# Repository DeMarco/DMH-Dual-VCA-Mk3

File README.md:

# DMH-Dual-VCA-Mk3
Version 3 of my stereo VCA in Kosmo format, now including voltage controlled panning and optional clipping and distortion!

## Features

- 2 channels, A and B
- 2 CV inputs per channel, each one with its own attenuverter knob
- Unipolar control voltage: 0V means VCA is fully closed (gain = 0), +10V means completely open (gain = 1)
- 1 offset knob per channel, useful to bias bipolar CV signals like those from LFOs
- The offset setting and attenuverted CV inputs of each channel are summed
- Toggle switches to select between pan/balanced/tremolo mode, and clipping/distortion
- Pan mode: output volue of both channels is halved. Pan CV signal will increase one channel's volume and decrease the other's simultaneously.
- Balanced mode: same as Pan mode, but both channels volume are biased with half the Pan CV signal amplitude, which preserves overall volume during panning.
- Tremolo mode: both channels duck in response to Pan CV.
- The Pan knob can be used to manually change panning when no Pan CV is plugged in. It becomes an attenuverter when Pan CV is used.
- Clip mode: 4v7 Zener diode pairs are applied to both channel outputs, effectively limiting output to about +/-5V.
- Distorted mode: 3v0 Zener diode pairs and 2x gain is applied to both channels output, effectively distorting and limiting output to +/-5V.
- LEDs indicate when the output levels pre-clipping/distortion peak above 5V, so you know that Clip mode is clipping the output when engaged.

Demo video: https://www.instagram.com/reel/DbrHDk0sg0o/?utm_source=ig_web_copy_link&igsh=MzRlODBiNWFlZA==

## Schematic and Gerbers

https://github.com/DeMarco/DMH-Dual-VCA-Mk3/blob/main/Schematic.pdf

https://github.com/DeMarco/DMH-Dual-VCA-Mk3/tree/main/Gerbers

https://github.com/DeMarco/DMH-Dual-VCA-Mk3/blob/main/DMH_Output_BoM.csv

Please note the plug-in VCA submodules are part of another Repo. You need to make 4 of these to assemble the complete module:

https://github.com/DeMarco/DMH-Submodules/tree/main/DMH_Submodule_VCA/Gerbers

## Assembly instructions

Use 11mm long pin headers on the Main PCB to ensure connection with the pin sockets on the Controls PCB.
Other than that, nothing special.
I recommend soldering components in order of height: start with resistors and diodes, then move on to IC sockets, capacitors, transistors and connectors.

### Main PCB

### Controls PCB

### VCA Submodule Mk1

## Calibration

### Attenuverters pot center

t.b.w.

### VCAs symmetry

t.b.w

## Current consumption

+12V --> 38mA

-12V --> 38mA

## Dimensions

Height: 20cm

Width: 5cm

Depth: t.b.c.

## Font

For viewing/customizing in KiCad, I recommend downloading and installing the Nulshock font from Typodermic: https://typodermicfonts.com/nulshock/

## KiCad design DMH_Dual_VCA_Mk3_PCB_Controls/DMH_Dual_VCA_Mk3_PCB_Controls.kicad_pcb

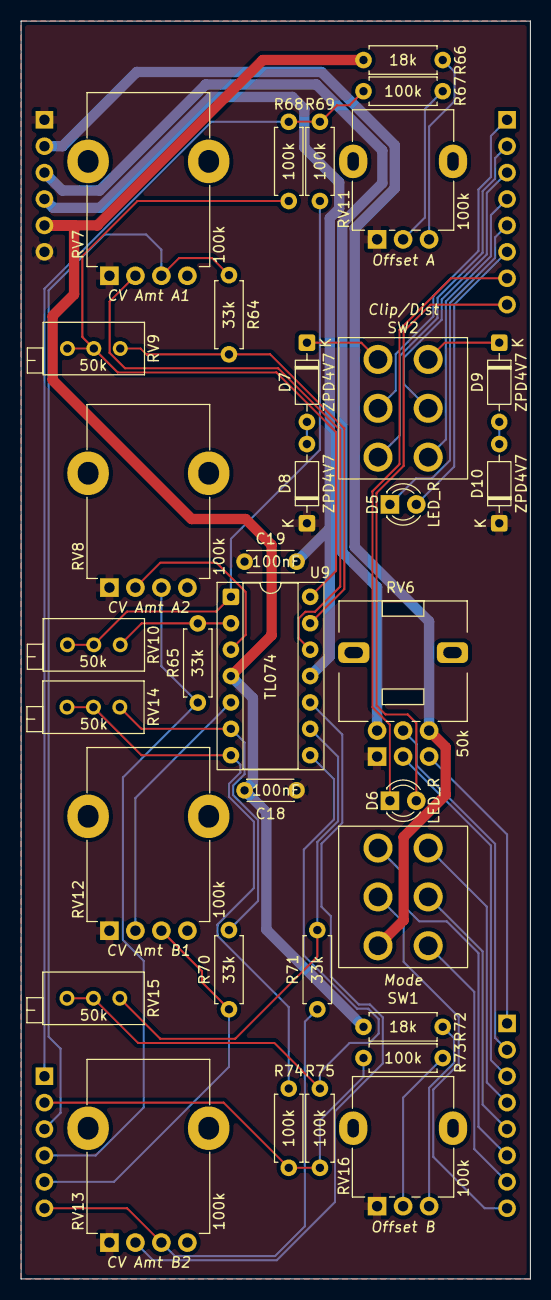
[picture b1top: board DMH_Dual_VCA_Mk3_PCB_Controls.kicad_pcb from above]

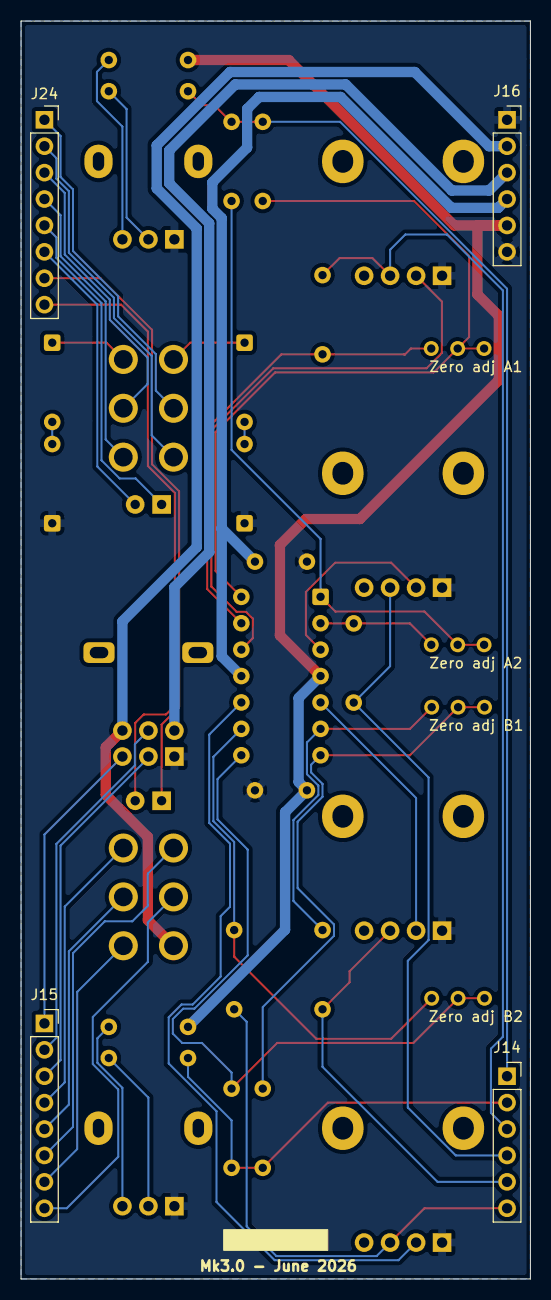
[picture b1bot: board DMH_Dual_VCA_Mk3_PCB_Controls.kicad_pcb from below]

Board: 2 copper layers, 49.0 x 121.0 mm, 38 parts (4 on the bottom side), 47 nets.

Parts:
C18, C19: 100nF; C_Disc_D4.3mm_W1.9mm_P5.00mm
D5, D6: LED_R; LED_D3.0mm
D7, D8, D9, D10: ZPD4V7; D_DO-35_SOD27_P7.62mm_Horizontal
J14, J16: Conn_01x06; PinSocket_1x06_P2.54mm_Vertical
J15, J24: Conn_01x08; PinSocket_1x08_P2.54mm_Vertical
R64, R65, R70, R71: 33k; R_Axial_DIN0207_L6.3mm_D2.5mm_P7.62mm_Horizontal
R66, R72: 18k; R_Axial_DIN0207_L6.3mm_D2.5mm_P7.62mm_Horizontal
R67, R68, R69, R73, R74, R75: 100k; R_Axial_DIN0207_L6.3mm_D2.5mm_P7.62mm_Horizontal
RV6: 50k; Potentiometer_Alps_RK09L_Double_Vertical
RV7, RV8, RV12, RV13: 100k; Potentiometer_TT_P110KH1
RV9, RV10, RV14, RV15: 50k; Potentiometer_Bourns_3296X_Horizontal
RV11, RV16: 100k; Potentiometer_Alpha_RD901F-40-00D_Single_Vertical
SW1: SW_DPDT_3way; Toggle_Switch_2_Poles_TE
SW2: SW_DPDT_OnOffOn_x2; Toggle_Switch_2_Poles_TE
U9: TL074; DIP-14_W7.62mm_Socket

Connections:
+5V: J16.2, RV6.6, SW1.1 (A)
+12V: C18.1, J16.5, R66.2, R72.2, U9.4 (V+)
-5V: J16.3, RV6.4
-12V: C19.2, J16.4, U9.11 (V-)
/Attenuverted_CV_PT_c: J15.4, SW1.6 (C)
/Balanced_Offset_c: J15.6, SW1.3 (C)
/CV_In_A1_c: J14.3, R64.1, RV7.3
/CV_In_A2_c: J14.4, R65.1, RV8.3
/CV_In_B1_c: J14.5, R70.1, RV12.3
/CV_In_B2_c: J14.6, R71.1, RV13.3
/CV_In_PT_c: J15.1, RV6.3
/CV_PT_Offset_c: J15.8, SW1.2 (B)
/CV_PT_Pot_G1_c: J15.3, RV6.2
/CV_PT_Pot_G2_c: J15.2, RV6.5
/Clipping/Clip_Sw_p1_c: J24.2, SW2.1 (A)
/Clipping/Clip_Sw_p2_c: J24.1, SW2.2 (B)
/Clipping/Clip_Sw_p4_c: J24.4, SW2.4 (A)
/Clipping/Clip_Sw_p5_c: J24.3, SW2.5 (B)
/Clipping/LED_A_pA_c: D5.2 (A), J24.6
/Clipping/LED_A_pK_c: D5.1 (K), J24.5
/Clipping/LED_B_pA_c: D6.2 (A), J24.8
/Clipping/LED_B_pK_c: D6.1 (K), J24.7
/Inverted_CV_PT_c: J15.7, SW1.4 (A)
/Processed_CV_A_c: J14.1, R67.2, R68.2, R69.2
/Processed_CV_B_c: J14.2, R73.2, R74.2, R75.2
/Processed_CV_PT_c: J15.5, SW1.5 (B)
GND: C18.2, C19.1, D8.1 (K), D10.1 (K), J16.1, J16.6, RV6.1, RV7.1, RV8.1, RV11.1, RV12.1, RV13.1, RV16.1
unnamed: D7.2 (A), D8.2 (A)
unnamed: D7.1 (K), SW2.3 (C)
unnamed: D9.1 (K), SW2.6 (C)
unnamed: D9.2 (A), D10.2 (A)
unnamed: R66.1, RV11.3
unnamed: R67.1, RV11.2
unnamed: R68.1, RV9.2, RV9.3, U9.14
unnamed: R69.1, RV10.2, RV10.3, U9.1
unnamed: R72.1, RV16.3
unnamed: R73.1, RV16.2
unnamed: R74.1, RV14.2, RV14.3, U9.7
unnamed: R75.1, RV15.2, RV15.3, U9.8
unnamed: RV8.2, U9.3 (+)
unnamed: R65.2, RV10.1, U9.2 (-)
unnamed: RV12.2, U9.5 (+)
unnamed: R70.2, RV14.1, U9.6 (-)
unnamed: RV13.2, U9.10 (+)
unnamed: R71.2, RV15.1, U9.9 (-)
unnamed: RV7.2, U9.12 (+)
unnamed: R64.2, RV9.1, U9.13 (-)

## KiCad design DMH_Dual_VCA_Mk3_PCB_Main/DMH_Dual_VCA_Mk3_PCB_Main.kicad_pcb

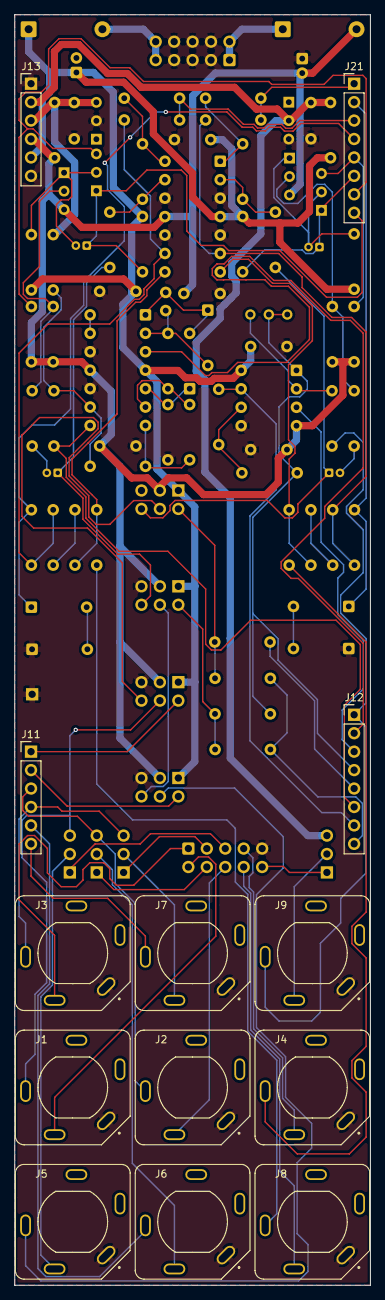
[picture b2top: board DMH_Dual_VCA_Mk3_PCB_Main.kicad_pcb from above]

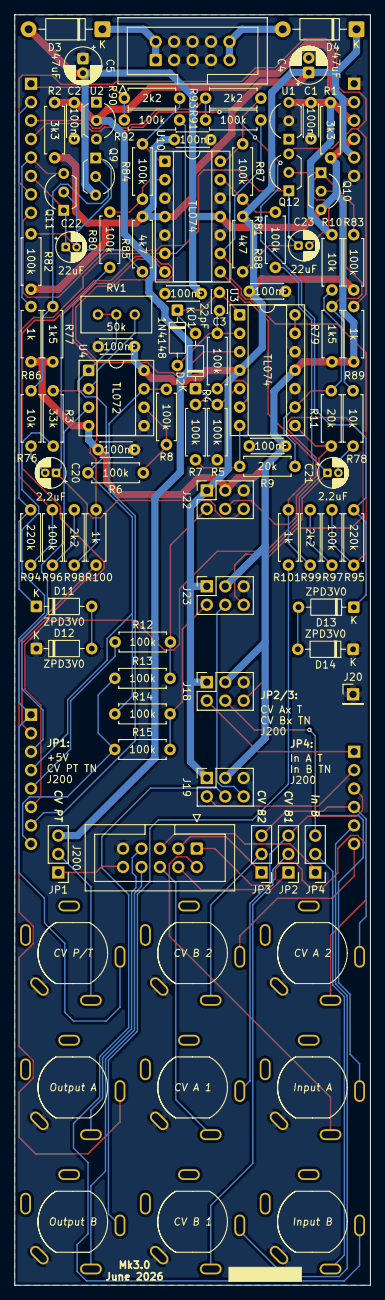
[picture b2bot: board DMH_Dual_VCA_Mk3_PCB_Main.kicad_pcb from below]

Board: 2 copper layers, 49.0 x 175.0 mm, 98 parts (85 on the bottom side), 79 nets.

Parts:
C1, C2, C6, C7, C8, C9, C24, C25: 100nF; C_Disc_D4.3mm_W1.9mm_P5.00mm
C3: 22pF; C_Disc_D3.0mm_W2.0mm_P2.50mm
C4, C5: 47uF; CP_Radial_D5.0mm_P2.00mm
C20, C21: 2.2uF; CP_Radial_D4.0mm_P1.50mm
C22, C23: 22uF; CP_Radial_D4.0mm_P1.50mm
D1, D2: 1N4148; D_DO-35_SOD27_P7.62mm_Horizontal
D3, D4: SB140; D_DO-41_SOD81_P10.16mm_Horizontal
D11, D12, D13, D14: ZPD3V0; D_DO-35_SOD27_P7.62mm_Horizontal
J1, J2, J3, J4, J5, J6, J7, J8, J9: TRS_Jack_6.35mm_Sw; CUI_SJ-63083D
J11, J13: Conn_01x06; PinHeader_1x06_P2.54mm_Vertical
J12, J21: Conn_01x08; PinHeader_1x08_P2.54mm_Vertical
J18, J19, J22, J23: Conn_02x03_Odd_Even; PinSocket_2x03_P2.54mm_Vertical
J20: Conn_01x01; PinHeader_1x01_P2.54mm_Vertical
J100: IDC_02x05; IDC-Header_2x05_P2.54mm_Vertical_Eurorack
J200: IDC_02x05; IDC-Header_2x05_P2.54mm_Vertical_BackBone
JP1, JP2, JP3, JP4: Jumper; PinHeader_1x03_P2.54mm_Vertical
Q9, Q10, Q11, Q12: BC548; TO-92L_Inline_Wide
R1, R2: 3k3; R_Axial_DIN0207_L6.3mm_D2.5mm_P7.62mm_Horizontal
R3: 33k; R_Axial_DIN0207_L6.3mm_D2.5mm_P7.62mm_Horizontal
R4, R5, R6, R7, R8, R12, R13, R14, R15, R80, R81, R82, R83, R84, R87, R92, R93, R96, R97: 100k; R_Axial_DIN0207_L6.3mm_D2.5mm_P7.62mm_Horizontal
R9, R11: 20k; R_Axial_DIN0207_L6.3mm_D2.5mm_P7.62mm_Horizontal
R10, R76, R78: 10k; R_Axial_DIN0207_L6.3mm_D2.5mm_P7.62mm_Horizontal
R77, R79: 1k5; R_Axial_DIN0207_L6.3mm_D2.5mm_P7.62mm_Horizontal
R85, R88: 4k7; R_Axial_DIN0207_L6.3mm_D2.5mm_P7.62mm_Horizontal
R86, R89, R100, R101: 1k; R_Axial_DIN0207_L6.3mm_D2.5mm_P7.62mm_Horizontal
R90, R91, R98, R99: 2k2; R_Axial_DIN0207_L6.3mm_D2.5mm_P7.62mm_Horizontal
R94, R95: 220k; R_Axial_DIN0207_L6.3mm_D2.5mm_P7.62mm_Horizontal
RV1: 50k; Potentiometer_Bourns_3296W_Vertical
U1, U2: LM4040LP-5; TO-92L_Inline_Wide
U3, U10: TL074; DIP-14_W7.62mm_Socket
U4: TL072; DIP-8_W7.62mm_Socket

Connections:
+5V: C2.1, J13.2, JP1.3 (B), R2.1, U2.2 (K)
+12V: C4.1, C6.1, C8.1, C24.1, D4.1 (K), J13.5, J18.1, J19.1, J22.1, J23.1, R2.2, R82.2, R83.2, R85.2, R88.2, U3.4 (V+), U4.8 (V+), U10.4 (V+)
-5V: C1.1, J13.3, R1.1, R10.1, U1.3 (A)
-12V: C5.2, C7.2, C9.2, C25.2, D3.2 (A), J13.4, J18.3, J19.3, J22.3, J23.3, Q9.3 (E), Q10.3 (E), R1.2, R77.1, R79.1, R86.1, R89.1, U3.11 (V-), U4.4 (V-), U10.11 (V-)
/Attenuverted_CV_PT_m: J12.4, R6.1, R14.1, RV1.2, RV1.3, U4.1
/Balanced_Offset_m: J12.6, R11.1, U3.8
/CV_In_A1_N_m: J2.TN (2), J200.8
/CV_In_A1_m: J2.T (3), J11.3, JP2.3 (B)
/CV_In_A2_N_m: J3.TN (2), J200.1
/CV_In_A2_m: J3.T (3), J11.4, JP3.3 (B)
/CV_In_B1_N_m: J6.TN (2), JP2.2 (C)
/CV_In_B1_m: J6.T (3), J11.5
/CV_In_B2_N_m: J7.TN (2), JP3.2 (C)
/CV_In_B2_m: J7.T (3), J11.6
/CV_In_PT_N_m: J9.TN (2), JP1.2 (C)
/CV_In_PT_m: J9.T (3), J12.1, R3.1
/CV_PT_Offset_m: J12.8, R13.1, R15.1
/CV_PT_Pot_G1_m: J12.3, U4.3 (+)
/CV_PT_Pot_G2_m: J12.2, U3.3 (+)
/Clip_In_A_m: C20.1, J22.6, R80.1
/Clip_In_B_m: C21.1, J23.6, R81.1
/Clip_Out_A_m: J4.T (3), R100.2
/Clip_Out_B_m: J8.T (3), R101.2
/Clipping/Clip_Sw_p1_m: D11.1 (K), J21.2, R94.1
/Clipping/Clip_Sw_p2_m: J21.1, R90.2, R92.1
/Clipping/Clip_Sw_p4_m: D13.1 (K), J21.4, R95.1
/Clipping/Clip_Sw_p5_m: J21.3, R91.2, R93.1
/Clipping/LED_A_pA_m: C22.1, J21.6, Q11.1 (C), R85.1
/Clipping/LED_A_pK_m: J21.5, Q11.3 (E), R86.2
/Clipping/LED_B_pA_m: C23.1, J21.8, Q12.1 (C), R88.1
/Clipping/LED_B_pK_m: J21.7, Q12.3 (E), R89.2
/Input_A_N_m: J1.TN (2), J200.6
/Input_A_m: J1.T (3), J18.4, JP4.3 (B)
/Input_B_N_m: J5.TN (2), JP4.2 (C)
/Input_B_m: J5.T (3), J19.4
/Inverted_CV_PT_m: J12.7, R8.2, U4.7
/Output_A_N_m: J4.TN (2), J200.4
/Output_B_N_m: J8.TN (2), J200.9
/Processed_CV_A_m: J11.1, J18.2
/Processed_CV_B_m: J11.2, J19.2
/Processed_CV_PT_m: J12.5, R12.1
/VCA_A_Tier1/Signal_Out: J18.6, J22.4
/VCA_A_Tier2/CV_Mix_In: J22.2, R12.2, R13.2
/VCA_B_Tier1/Signal_Out: J19.6, J23.4
/VCA_B_Tier2/CV_Mix_In: J23.2, R14.2, R15.2
GND: C1.2, C2.2, C4.2, C5.1, C6.2, C7.1, C8.2, C9.1, C24.2, C25.1, D12.1 (K), D14.1 (K), J1.S (1), J2.S (1), J3.S (1), J4.S (1), J5.S (1), J6.S (1), J7.S (1), J8.S (1), J9.S (1), J13.1, J13.6, J18.5, J19.5, J20.1 (Pin_1_1), J22.5, J23.5, J100.2a, J100.2b, J100.3a, J100.3b, J100.4a, J100.4b, J200.5, R5.2, U1.2 (K), U2.3 (A), U3.10 (+), U3.12 (+), U4.5 (+), U10.3 (+), U10.5 (+), U10.10 (+), U10.12 (+)
unnamed: C20.2, R76.2
unnamed: C21.2, R78.2
unnamed: C3.2, D1.2 (A), R4.2, U3.2 (-)
unnamed: C3.1, D1.1 (K), D2.2 (A), U3.1
unnamed: D2.1 (K), R5.1, U3.5 (+)
unnamed: D3.1 (K), J100.1a, J100.1b
unnamed: D4.2 (A), J100.5a, J100.5b
unnamed: D11.2 (A), D12.2 (A)
unnamed: D13.2 (A), D14.2 (A)
unnamed: J200.2, JP3.1 (A)
unnamed: J200.3, JP4.1 (A)
unnamed: J200.7, JP2.1 (A)
unnamed: J200.10, JP1.1 (A)
unnamed: Q9.2 (B), R76.1, R77.2
unnamed: Q10.2 (B), R78.1, R79.2
unnamed: C23.2, Q10.1 (C), Q12.2 (B), R83.1
unnamed: C22.2, Q9.1 (C), Q11.2 (B), R82.1
unnamed: R7.1, R9.2, U3.7
unnamed: R84.1, R90.1, U10.1
unnamed: R87.1, R91.1, U10.14
unnamed: R96.2, R98.1
unnamed: R97.2, R99.1
unnamed: R98.2, R100.1, U10.7
unnamed: R99.2, R101.1, U10.8
unnamed: R4.1, R7.2, U3.6 (-)
unnamed: R9.1, R10.2, R11.2, U3.9 (-)
unnamed: U3.13 (-), U3.14
unnamed: R3.2, RV1.1, U4.2 (-)
unnamed: R6.2, R8.1, U4.6 (-)
unnamed: R80.2, R84.2, U10.2 (-)
unnamed: R92.2, R94.2, R96.1, U10.6 (-)
unnamed: R93.2, R95.2, R97.1, U10.9 (-)
unnamed: R81.2, R87.2, U10.13 (-)

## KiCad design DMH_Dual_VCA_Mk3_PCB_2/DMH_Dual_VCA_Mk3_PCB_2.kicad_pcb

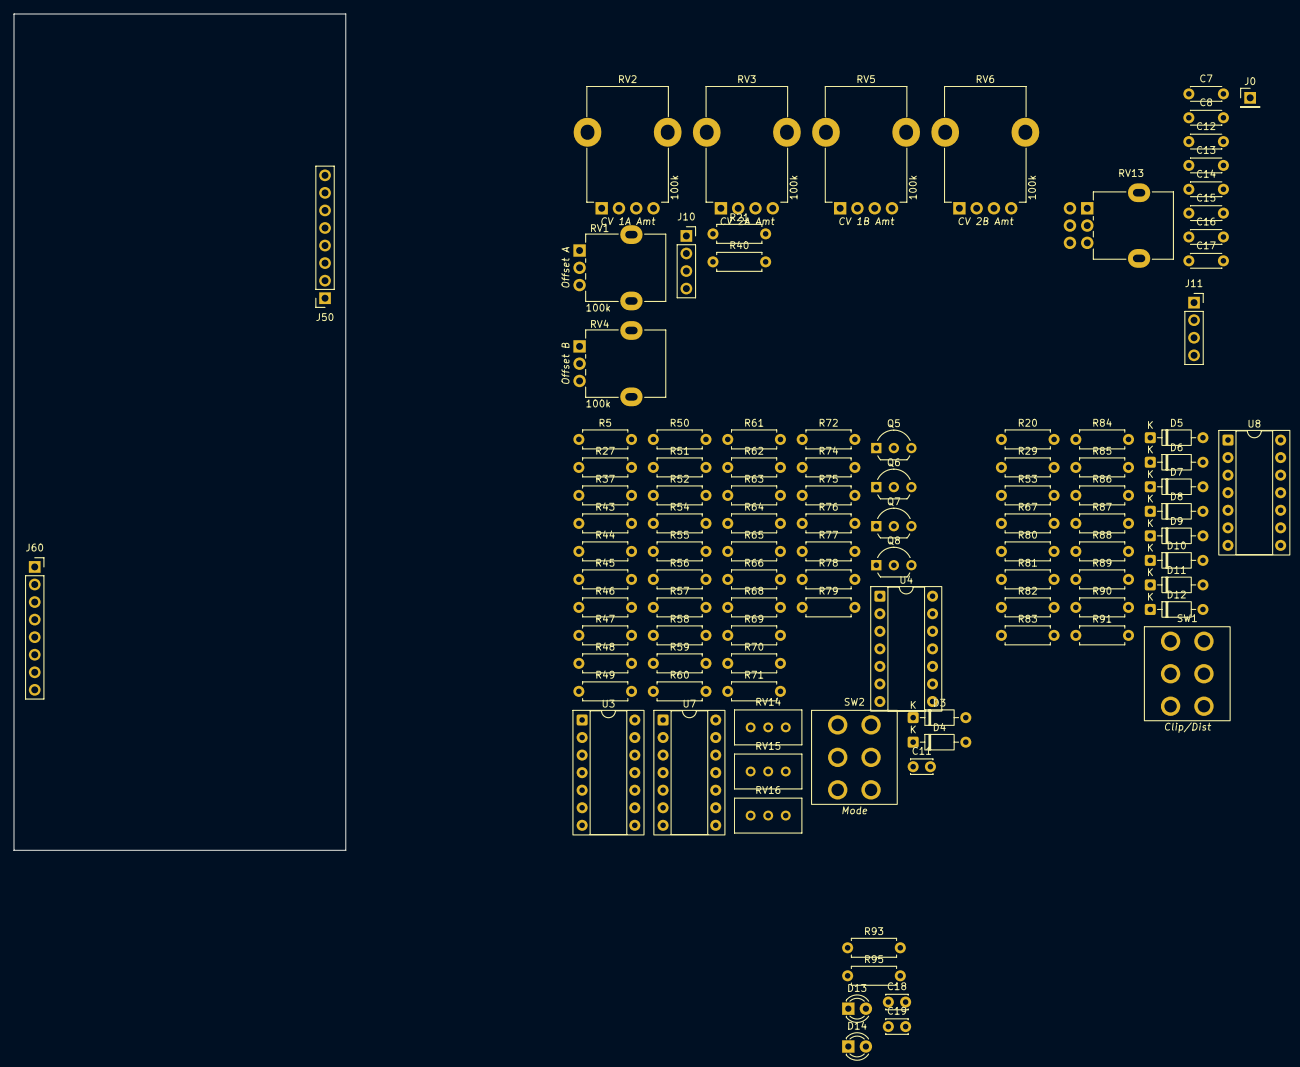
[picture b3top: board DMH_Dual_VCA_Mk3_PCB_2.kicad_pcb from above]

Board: 2 copper layers, 48.0 x 121.0 mm, 105 parts (0 on the bottom side), 84 nets, no tracks yet.

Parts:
C7, C8, C12, C13, C14, C15, C16, C17: 100nF; C_Disc_D4.3mm_W1.9mm_P5.00mm
C11: 22pF; C_Disc_D3.0mm_W2.0mm_P2.50mm
C18, C19: 100pF; C_Disc_D3.0mm_W2.0mm_P2.50mm
D3, D4: 1N4148; D_DO-35_SOD27_P7.62mm_Horizontal
D5, D6, D7, D8: ZPD4V7; D_DO-35_SOD27_P7.62mm_Horizontal
D9, D10, D11, D12: ZPD3V0; D_DO-35_SOD27_P7.62mm_Horizontal
D13, D14: LED_R; LED_D3.0mm
J0: Conn_01x01; PinHeader_1x01_P2.54mm_Vertical
J10: Conn_01x04; PinSocket_1x04_P2.54mm_Vertical
J11: Conn_01x04_PinHeader; PinSocket_1x04_P2.54mm_Vertical
J50, J60: Conn_01x08; PinSocket_1x08_P2.54mm_Vertical
Q5, Q6, Q7, Q8: BC548; TO-92L_Inline_Wide
R5, R27, R37, R50, R51, R52, R54, R55, R56, R64, R65, R66, R69, R70, R71, R72, R74, R75, R76, R80, R81, R85, R87: 100k; R_Axial_DIN0207_L6.3mm_D2.5mm_P7.62mm_Horizontal
R20, R84, R88, R89, R93, R95: 2k2; R_Axial_DIN0207_L6.3mm_D2.5mm_P7.62mm_Horizontal
R21, R40: 18k; R_Axial_DIN0207_L6.3mm_D2.5mm_P7.62mm_Horizontal
R29, R44, R46, R53, R58, R60, R67, R77, R78, R83: 20k; R_Axial_DIN0207_L6.3mm_D2.5mm_P7.62mm_Horizontal
R43, R47, R57, R63: 100R; R_Axial_DIN0207_L6.3mm_D2.5mm_P7.62mm_Horizontal
R45, R48, R49, R59, R61, R62, R79: 10k; R_Axial_DIN0207_L6.3mm_D2.5mm_P7.62mm_Horizontal
R68: 33k; R_Axial_DIN0207_L6.3mm_D2.5mm_P7.62mm_Horizontal
R82, R86: 220k; R_Axial_DIN0207_L6.3mm_D2.5mm_P7.62mm_Horizontal
R90, R91: 1k; R_Axial_DIN0207_L6.3mm_D2.5mm_P7.62mm_Horizontal
RV1, RV4: 100k; Potentiometer_Alpha_RD901F-40-00D_Single_Vertical
RV2, RV3, RV5, RV6: 100k; Potentiometer_TT_P110KH1
RV13: 100k; Potentiometer_Alpha_RD902F-40-00D_Dual_Vertical
RV14, RV15: 100k; Potentiometer_Bourns_3296W_Vertical
RV16: 50k; Potentiometer_Bourns_3296W_Vertical
SW1: SW_DPDT_OnOffOn_x2; Toggle_Switch_2_Poles_TE
SW2: SW_DPDT_3way; Toggle_Switch_2_Poles_TE
U3, U4, U7, U8: TL074; DIP-14_W7.62mm_Socket

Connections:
+5V: J10.1, RV13.6, SW2.1 (A), U4.9 (-), U4.13 (-)
+12V: C7.1, C12.1, C14.1, C16.1, J50.3, J60.3, R21.2, R40.2, R44.2, R46.2, R58.2, R60.2, RV14.3, RV15.3, U3.4 (V+), U4.4 (V+), U7.4 (V+), U8.4 (V+)
-5V: J10.2, R79.1, RV13.4
-12V: C8.2, C13.2, C15.2, C17.2, J50.7, J60.7, RV14.1, RV15.1, U3.11 (V-), U4.11 (V-), U7.11 (V-), U8.11 (V-)
/2nd VCA/Attenuverted CV PT: R54.1, R69.1, RV16.2, RV16.3, SW2.6 (C), U4.1
/2nd VCA/Balanced Offset: R78.1, SW2.3 (C), U7.8
/2nd VCA/CV PT Input: J10.3, R68.1, RV13.3
/2nd VCA/CV PT Offset: R5.1, R71.1, SW2.2 (B)
/2nd VCA/CV PT Pot G1: RV13.2, U4.3 (+)
/2nd VCA/CV PT Pot G2: RV13.5, U7.3 (+)
/2nd VCA/Input A: J11.1, R37.2
/2nd VCA/Input B: J11.4, R56.2
/2nd VCA/Inverted CV PT: R70.2, SW2.4 (A), U4.7
/2nd VCA/Output A: R52.1, R53.1, U3.8
/2nd VCA/Output B: R29.1, R66.1, U3.7
/Clipping/Output A: J11.2, R90.2
/Clipping/Output B: J11.3, R91.2
/Inputs and Outputs/CV 1 A Jack: J50.1, RV2.3
/Inputs and Outputs/CV 1 A Pot: J50.5, RV2.2
/Inputs and Outputs/CV 1 B Jack: J60.1, RV5.3
/Inputs and Outputs/CV 1 B Pot: J60.5, RV5.2
/Inputs and Outputs/CV 2 A Jack: J50.2, RV3.3
/Inputs and Outputs/CV 2 A Pot: J50.6, RV3.2
/Inputs and Outputs/CV 2 B Jack: J60.2, RV6.3
/Inputs and Outputs/CV 2 B Pot: J60.6, RV6.2
/Inputs and Outputs/Offset A Pot: J50.4, RV1.2
/Inputs and Outputs/Offset B Pot: J60.4, RV4.2
GND: C7.2, C8.1, C12.2, C13.1, C14.2, C15.1, C16.2, C17.1, D6.1 (K), D8.1 (K), D10.1 (K), D12.1 (K), D13.1 (K), D14.1 (K), J0.1, J10.4, J50.8, J60.8, R43.1, R47.1, R51.2, R57.1, R63.1, R65.2, R76.2, RV1.1, RV2.1, RV3.1, RV4.1, RV5.1, RV6.1, RV13.1, U3.3 (+), U3.12 (+), U4.5 (+), U7.10 (+), U7.12 (+), U8.3 (+), U8.5 (+), U8.10 (+), U8.12 (+)
unnamed: C18.2, R93.1, U4.8
unnamed: C19.2, R95.1, U4.14
unnamed: C11.2, D3.2 (A), R74.2, U7.2 (-)
unnamed: C11.1, D3.1 (K), D4.2 (A), U7.1
unnamed: D4.1 (K), R76.1, U7.5 (+)
unnamed: D5.2 (A), D6.2 (A)
unnamed: D5.1 (K), SW1.3 (C)
unnamed: D7.2 (A), D8.2 (A)
unnamed: D7.1 (K), SW1.6 (C)
unnamed: D9.1 (K), R82.1, SW1.1 (A)
unnamed: D9.2 (A), D10.2 (A)
unnamed: D11.2 (A), D12.2 (A)
unnamed: D11.1 (K), R86.1, SW1.4 (A)
unnamed: D13.2 (A), R93.2
unnamed: D14.2 (A), R95.2
unnamed: Q5.2 (B), R37.1, R43.2
unnamed: Q5.1 (C), R44.1, R48.2
unnamed: Q5.3 (E), Q6.3 (E), R45.2
unnamed: Q6.2 (B), R47.2, R50.2
unnamed: Q6.1 (C), R46.1, R49.2
unnamed: Q7.2 (B), R56.1, R57.2
unnamed: Q7.1 (C), R58.1, R61.2
unnamed: Q7.3 (E), Q8.3 (E), R59.2
unnamed: Q8.2 (B), R63.2, R64.2
unnamed: Q8.1 (C), R60.1, R62.2
unnamed: R20.1, R67.1, U8.1
unnamed: R21.1, RV1.3
unnamed: R27.2, R59.1, U3.1
unnamed: R40.1, RV4.3
unnamed: R45.1, R72.2, U3.14
unnamed: R50.1, RV14.2
unnamed: R55.1, SW2.5 (B)
unnamed: R64.1, RV15.2
unnamed: R75.1, R77.2, U7.7
unnamed: R80.2, R88.1
unnamed: R83.1, R84.1, U8.14
unnamed: R87.2, R89.1
unnamed: R88.2, R90.1, U8.7
unnamed: R89.2, R91.1, U8.8
unnamed: R20.2, R81.1, SW1.2 (B)
unnamed: R84.2, R85.1, SW1.5 (B)
unnamed: R5.2, R27.1, R54.2, U3.2 (-)
unnamed: R62.1, R65.1, U3.5 (+)
unnamed: R61.1, R66.2, U3.6 (-)
unnamed: R49.1, R51.1, U3.10 (+)
unnamed: R48.1, R52.2, U3.9 (-)
unnamed: R55.2, R71.2, R72.1, U3.13 (-)
unnamed: R68.2, RV16.1, U4.2 (-)
unnamed: R69.2, R70.1, U4.6 (-)
unnamed: C18.1, R53.2, R67.2, U4.10 (+), U8.2 (-)
unnamed: C19.1, R29.2, R83.2, U4.12 (+), U8.13 (-)
unnamed: R74.1, R75.2, U7.6 (-)
unnamed: R77.1, R78.2, R79.2, U7.9 (-)
unnamed: U7.13 (-), U7.14
unnamed: R80.1, R81.2, R82.2, U8.6 (-)
unnamed: R85.2, R86.2, R87.1, U8.9 (-)

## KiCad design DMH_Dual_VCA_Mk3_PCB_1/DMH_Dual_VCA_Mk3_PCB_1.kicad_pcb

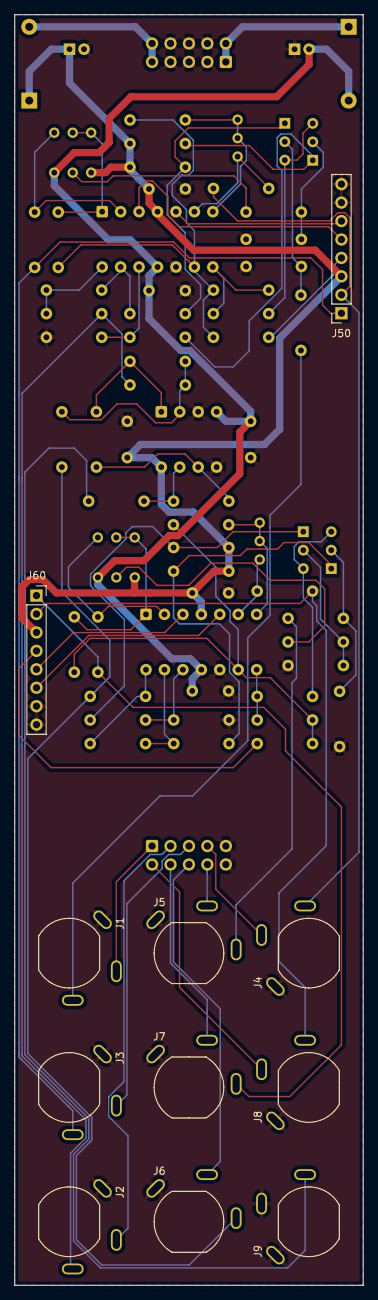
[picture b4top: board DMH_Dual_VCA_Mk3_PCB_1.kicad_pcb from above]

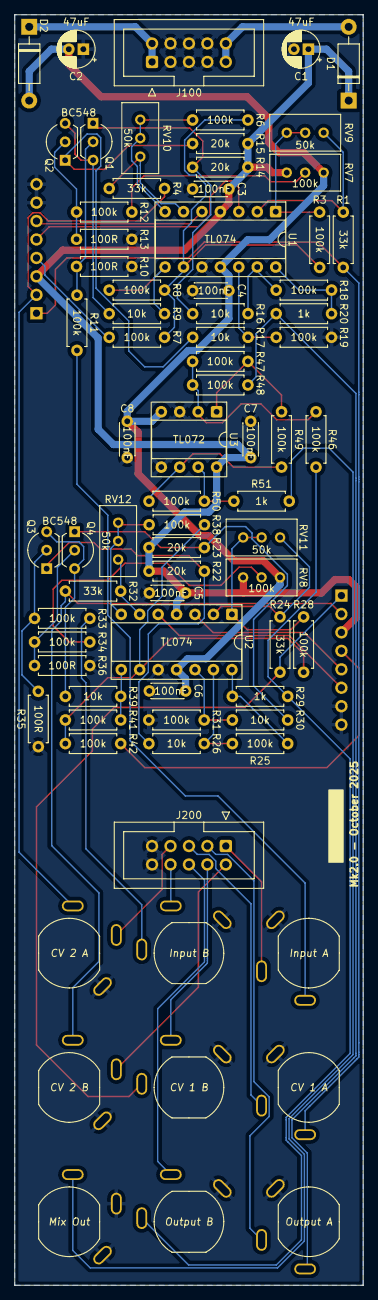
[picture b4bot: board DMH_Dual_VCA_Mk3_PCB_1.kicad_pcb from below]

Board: 2 copper layers, 48.0 x 175.0 mm, 78 parts (67 on the bottom side), 62 nets.

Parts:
C1, C2: 47uF; CP_Radial_D5.0mm_P2.00mm
C3, C4, C5, C6, C7, C8: 100nF; C_Disc_D4.3mm_W1.9mm_P5.00mm
D1: SB140+; D_DO-41_SOD81_P10.16mm_Horizontal
D2: SB140-; D_DO-41_SOD81_P10.16mm_Horizontal
J1, J2, J3, J4, J5, J6, J7, J8, J9: TS_Jack_6.35mm_Sw; CUI_MJ-63052A
J50, J60: Conn_01x08; PinSocket_1x08_P2.54mm_Vertical
J100: IDC_02x05; IDC-Header_2x05_P2.54mm_Vertical_Eurorack
J200: IDC_02x05; IDC-Header_2x05_P2.54mm_Vertical_BackBone
Q1, Q2, Q3, Q4: BC548; TO-92L_Inline_Wide
R1, R4, R24, R32: 33k; R_Axial_DIN0207_L6.3mm_D2.5mm_P7.62mm_Horizontal
R3, R6, R7, R8, R11, R12, R18, R19, R25, R28, R31, R33, R34, R38, R41, R42, R46, R47, R48, R49, R50: 100k; R_Axial_DIN0207_L6.3mm_D2.5mm_P7.62mm_Horizontal
R9, R16, R17, R26, R30, R39: 10k; R_Axial_DIN0207_L6.3mm_D2.5mm_P7.62mm_Horizontal
R10, R13, R35, R36: 100R; R_Axial_DIN0207_L6.3mm_D2.5mm_P7.62mm_Horizontal
R14, R15, R22, R23: 20k; R_Axial_DIN0207_L6.3mm_D2.5mm_P7.62mm_Horizontal
R20, R29, R51: 1k; R_Axial_DIN0207_L6.3mm_D2.5mm_P7.62mm_Horizontal
RV7, RV8: 100k; Potentiometer_Bourns_3296W_Vertical
RV9, RV10, RV11, RV12: 50k; Potentiometer_Bourns_3296W_Vertical
U1, U2: TL074; DIP-14_W7.62mm_Socket
U3: TL072; DIP-8_W7.62mm_Socket

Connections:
+12V: C1.1, C3.1, C5.1, C7.1, D1.1 (K), J50.3, J60.3, R14.2, R15.2, R22.2, R23.2, RV7.3, RV8.3, U1.4 (V+), U2.4 (V+), U3.8 (V+)
-12V: C2.2, C4.2, C6.2, C8.2, D2.2 (A), RV7.1, RV8.1, U1.11 (V-), U2.11 (V-), U3.4 (V-)
/Core Circuit A/CV 1 A Input: J3.T, J50.1, R1.1
/Core Circuit A/CV 1 A Pot: J50.5, U1.3 (+)
/Core Circuit A/CV 2 A Input: J4.T, J50.2, R4.1
/Core Circuit A/CV 2 A Pot: J50.6, U1.5 (+)
/Core Circuit A/Input A: J1.T, R11.2
/Core Circuit A/Offset A Pot: J50.4, R7.1
/Core Circuit A/Output A: J2.T, R20.1, R48.1
/Core Circuit B/CV 1 B Input: J7.T, J60.1, R24.1
/Core Circuit B/CV 1 B Pot: J60.5, U2.3 (+)
/Core Circuit B/CV 2 B Input: J8.T, J60.2, R32.1
/Core Circuit B/CV 2 B Pot: J60.6, U2.5 (+)
/Core Circuit B/Input B: J5.T, R33.2
/Core Circuit B/Offset B Pot: J60.4, R42.1
/Core Circuit B/Output B: J6.T, R29.1, R46.1
/Inputs and Outputs/Mix Out Jack: J9.T, R51.2
GND: C1.2, C2.1, C3.2, C4.1, C5.2, C6.1, C7.2, C8.1, J1.S, J2.S, J3.S, J4.S, J5.S, J6.S, J7.S, J8.S, J9.S, J9.TN, J50.7, J50.8, J60.7, J60.8, J100.2a, J100.2b, J100.3a, J100.3b, J100.4a, J100.4b, J200.5, J200.10, R10.1, R13.1, R19.2, R31.2, R35.1, R36.1, U1.10 (+), U2.10 (+), U3.3 (+), U3.5 (+)
unnamed: D1.2 (A), J100.5a, J100.5b
unnamed: D2.1 (K), J100.1a, J100.1b
unnamed: J1.TN, J200.1
unnamed: J2.TN, J200.2
unnamed: J3.TN, J200.3
unnamed: J4.TN, J200.4
unnamed: J8.TN, J200.6
unnamed: J7.TN, J200.7
unnamed: J6.TN, J200.8
unnamed: J5.TN, J200.9
unnamed: Q1.2 (B), R10.2, R11.1
unnamed: Q1.1 (C), R14.1, R16.2
unnamed: Q1.3 (E), Q2.3 (E), R9.2
unnamed: Q2.2 (B), R12.2, R13.2
unnamed: Q2.1 (C), R15.1, R17.2
unnamed: Q3.2 (B), R33.1, R35.2
unnamed: Q3.1 (C), R22.1, R26.2
unnamed: Q3.3 (E), Q4.3 (E), R39.2
unnamed: Q4.2 (B), R34.2, R36.2
unnamed: Q4.1 (C), R23.1, R30.2
unnamed: R3.1, RV9.2, RV9.3, U1.1
unnamed: R6.1, RV10.2, RV10.3, U1.7
unnamed: R8.2, R9.1, U1.8
unnamed: R12.1, RV7.2
unnamed: R18.1, R20.2, U1.14
unnamed: R25.1, R29.2, U2.14
unnamed: R28.1, RV11.2, RV11.3, U2.1
unnamed: R34.1, RV8.2
unnamed: R38.1, RV12.2, RV12.3, U2.7
unnamed: R39.1, R41.2, U2.8
unnamed: R47.2, R49.1, U3.1
unnamed: R50.2, R51.1, U3.7
unnamed: R1.2, RV9.1, U1.2 (-)
unnamed: R4.2, RV10.1, U1.6 (-)
unnamed: R3.2, R6.2, R7.2, R8.1, U1.9 (-)
unnamed: R17.1, R19.1, U1.12 (+)
unnamed: R16.1, R18.2, U1.13 (-)
unnamed: R24.2, RV11.1, U2.2 (-)
unnamed: R32.2, RV12.1, U2.6 (-)
unnamed: R28.2, R38.2, R41.1, R42.2, U2.9 (-)
unnamed: R30.1, R31.1, U2.12 (+)
unnamed: R25.2, R26.1, U2.13 (-)
unnamed: R46.2, R47.1, R48.2, U3.2 (-)
unnamed: R49.2, R50.1, U3.6 (-)

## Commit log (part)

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2026-03-16 Designed mk3 panel
    Added Pan/Tremolo switch and amount knob
    Added Clip switch
2026-03-16 Started PCB 2 project
2026-03-16 PCB 1 circuit design ongoing
2026-03-17 Mode switching design in progress
2026-03-19 2nd VCA design done
    Clipping design in progress
2026-03-20 Designed clip and dist circuit
2026-03-20 Synced PCB 1 and 2 schematics
2026-03-20 Added clipping LED to schematic
    Still need to add to Panel
2026-03-22 Improved clipping indication
2026-03-22 Positioned controls on PCB 2
2026-03-23 Synced PCB1 to PCB2
2026-03-23 Improved cipping indication LED drive
2026-04-12 Improved clipping indicator
2026-04-19 Created proper Controls PCB project
2026-05-15 Update SynthStuff
2026-05-19 KiCad 10 and updated SynthStuff
2026-05-19 Create design-block-lib-table
2026-05-22 Restarting schematic drawing
2026-05-23 Experimenting with VCA design blocks
2026-05-25 Redesigned schematic layout
2026-05-25 schematic labeling in progress
2026-05-25 Schematic redesign done
2026-05-25 Controls PCB comp placement started
2026-05-26 Moved clipping circuit back to main PCB
2026-05-27 Controls PCB comp placement in progress
2026-05-28 Controls PCB comp placement done
2026-05-28 Controls PCB routing done
2026-05-30 Started Main PCB comp placement
2026-05-30 Comp placement in progress
2026-05-30 Main comp placement in progress
2026-06-01 Main comp placement done
2026-06-01 Started Main PCB routing
2026-06-14 Added jumpers to normalize CV inputs B to A
2026-06-14 Fixed -5V supply circuit mistake
2026-06-16 Added jumper to normalize Input B to A
2026-06-19 Main PCB routing in progress
2026-06-19 Main PCB routing done
2026-06-20 Generated Gerbers
2026-06-20 Moved old versions to sub folder
2026-06-21 Corrected -5V symbol
